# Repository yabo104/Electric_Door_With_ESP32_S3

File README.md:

# Controlador de Portón — ESP32-S3

Controlador electrónico para automatizar la apertura y cierre de un portón residencial, con
firmware propio (ESP32-S3) y placa controladora diseñada a medida (KiCad).

Mueve el motor mediante dos relevos (sentido) y un TRIAC (potencia, por ángulo de fase
sincronizado al cruce por cero de la red), lee finales de carrera y un sensor de efecto Hall para
detectar movimiento/atasco, y decodifica un control remoto RF 433MHz.

## Estado actual

**Funcional en hardware real** — validado de punta a punta en un portón físico:

- Apertura y cierre con un solo botón del control remoto, con inversión de sentido y detención
  parcial (doble pulsación) para dejar pasar personas o vehículos sin abrir del todo.
- Interlock de seguridad: nunca ambos relevos activos a la vez, el motor siempre se detiene antes
  de invertir sentido.
- Detección de atasco por ausencia de pulsos del sensor de movimiento, con estado de falla y
  reset manual por un botón dedicado.
- Disparo del TRIAC por ángulo de fase, sincronizado al cruce por cero de la red — hoy en un
  **nivel de potencia fijo**, calibrado empíricamente en el portón real (ver *Limitaciones*).
- Indicador LED (encendido en movimiento, parpadeo al confirmar cada final de carrera) y un
  contador de pulsos por trayecto, pensado como base para una futura calibración de recorrido.
- Sin Wi-Fi ni Bluetooth: los dos radios se apagan explícitamente al arrancar.

### Limitaciones conocidas

- **Sin arranque/parada suaves todavía.** El disparo por ángulo de fase está implementado y
  funcionando, pero corre a potencia constante — la rampa gradual (arranque suave) quedó
  pospuesta: en las pruebas, disparar muy cerca del cruce por cero no enganchaba el TRIAC de
  forma confiable con este motor (carga inductiva), y la rampa pasaba por esa zona. La parada
  sigue siendo instantánea.
- El `timeout` de detección de atasco sigue en un valor ajustado empíricamente, no derivado
  analíticamente.
- El diseño de la placa (carpeta de KiCad) está en proceso de renombrado; los archivos de
  fabricación (gerbers/BOM) pueden no reflejar la última revisión del esquemático.

## Estructura del repositorio

- **`Firmware_Porton/`** — firmware, proyecto [PlatformIO](https://platformio.org/) (entorno
  `esp32-s3-devkitc-1`, framework Arduino).
- **`PCB_Door_Controller/`** — diseño de la placa controladora en KiCad.
- **`Docs/`** — datasheets y referencias de los componentes usados (driver TRIAC, convertidor
  DC-DC, módulo de alimentación).
- **`bitacora/`** — documentación de continuidad del proyecto (decisiones, arquitectura,
  histórico de sesiones de desarrollo) bajo el marco [stele](https://github.com/emezav/stele).

## Hardware

| Componente | Detalle |
| --- | --- |
| Módulo | ESP32-S3-WROOM-1U-N8R8 |
| Motor | AC 110V, fase partida (con capacitor de arranque) |
| Potencia | TRIAC BT138-800, disparo por ángulo de fase sincronizado a cruce por cero |
| Sentido | 2 relevos (interlock por software: nunca ambos activos) |
| Posición | 2 finales de carrera (reed switch) + sensor de efecto Hall |
| Control remoto | Receptor RF 433MHz (decodificado externamente, el ESP32-S3 lee canales digitales) |

## Arranque de desarrollo

```bash
cd Firmware_Porton
pio run                              # compilar
pio run -t upload --upload-port COMx # cargar a la placa
pio device monitor -p COMx -b 115200 # monitor serie (o el USB CDC nativo del ESP32-S3)
```

## Licencia

Sin definir todavía.

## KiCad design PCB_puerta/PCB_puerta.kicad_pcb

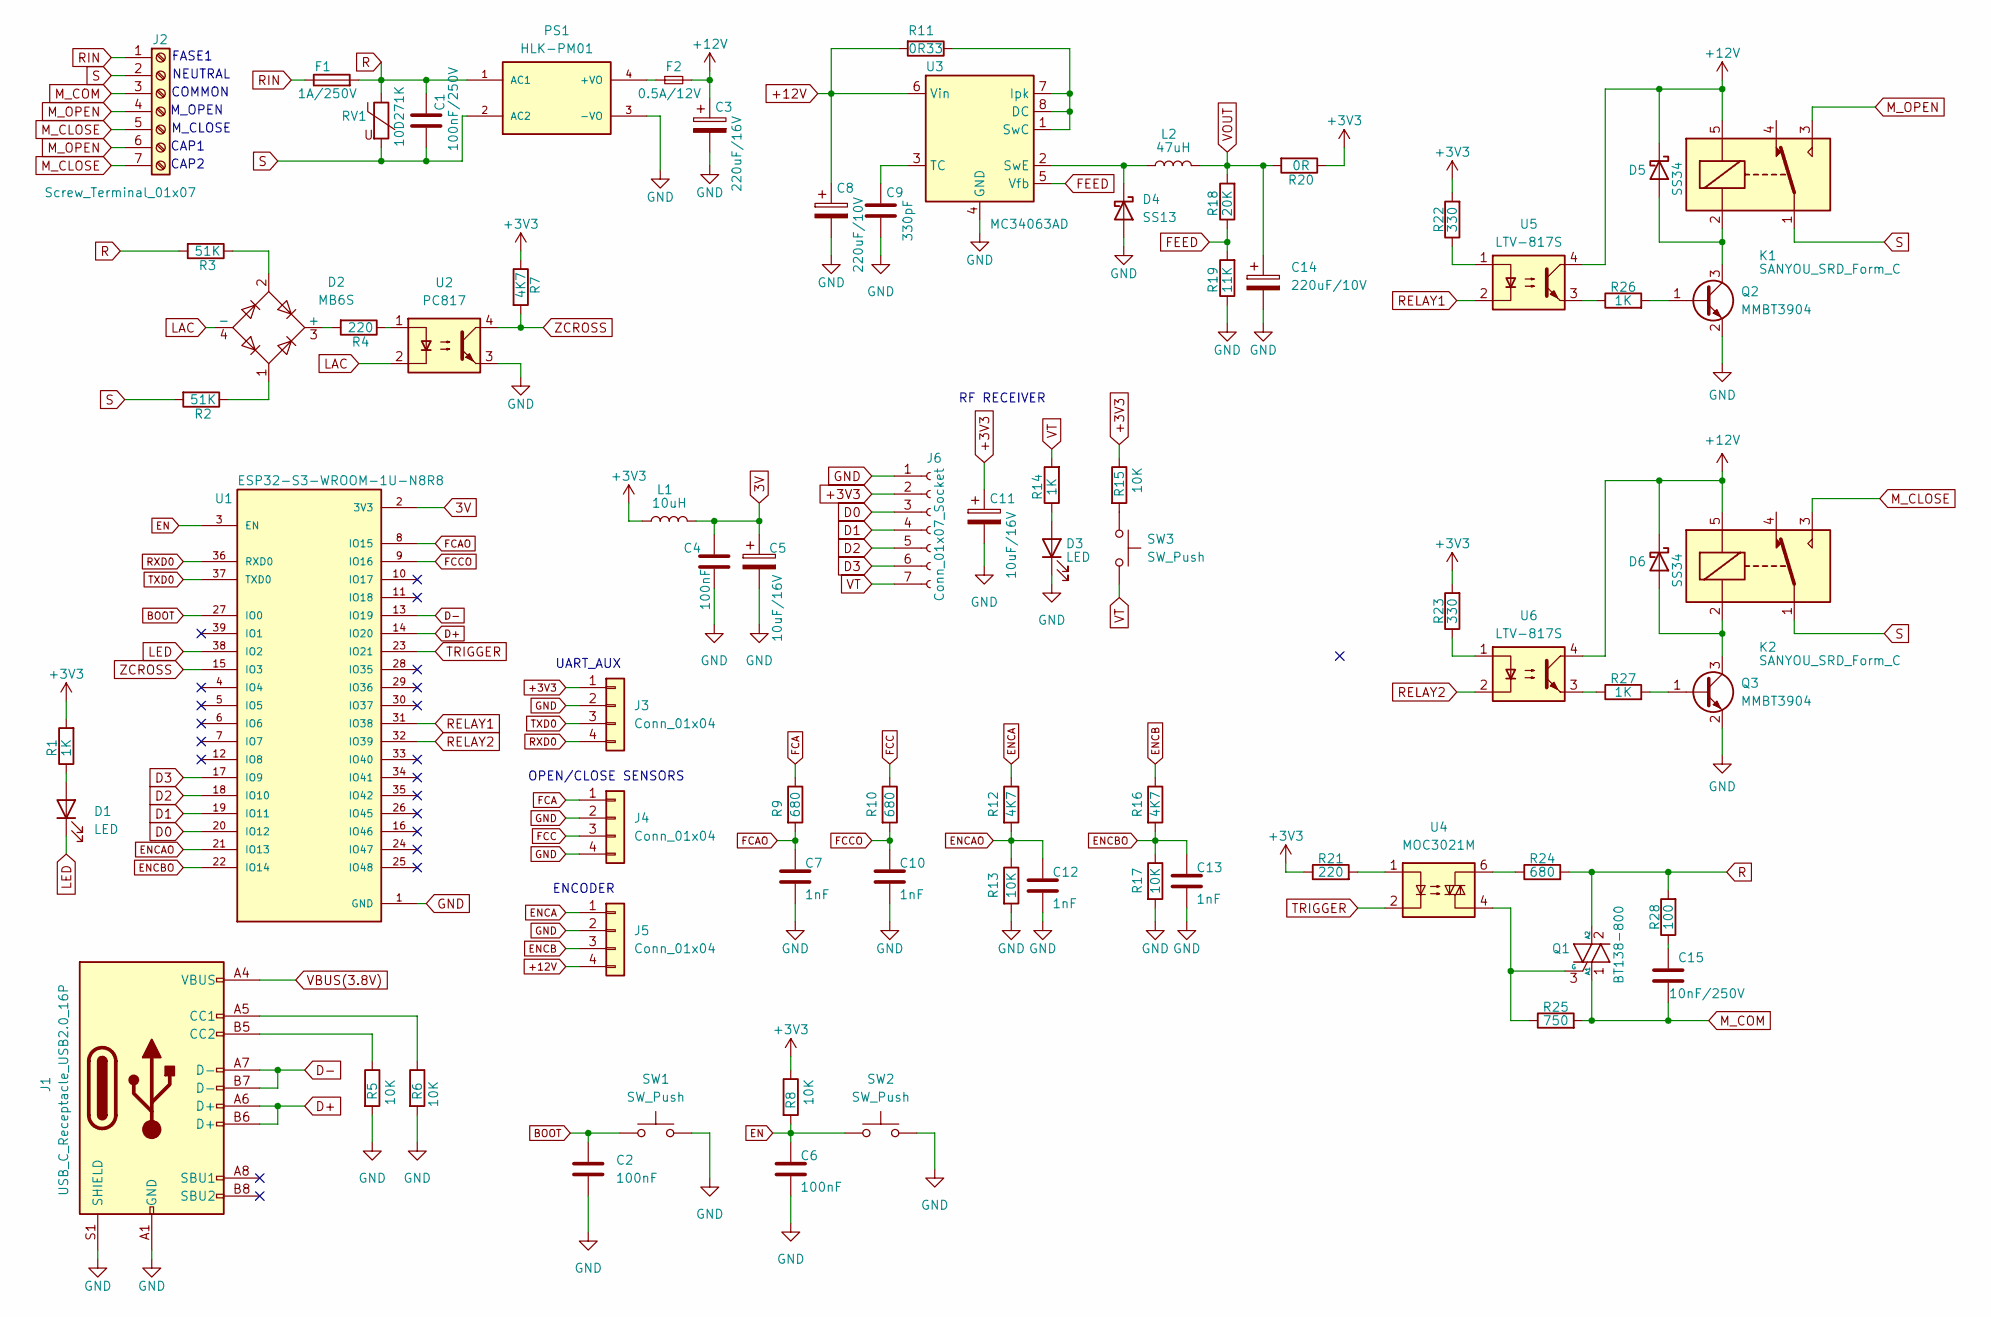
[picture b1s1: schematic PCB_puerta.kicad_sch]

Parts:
C1: 100nF/250V; C_Disc_D10.5mm_W5.0mm_P7.50mm
C2, C4, C6: 100nF; C_0603_1608Metric
C3: 220uF/16V; CP_Elec_6.3x7.7
C5, C11: 10uF/16V; CP_EIA-3216-10_Kemet-I
C7, C10, C12, C13: 1nF; C_0603_1608Metric
C8, C14: 220uF/10V; CP_Elec_6.3x7.7
C9: 330pF; C_0603_1608Metric
C15: 10nF/250V; C_Disc_D7.5mm_W5.0mm_P7.50mm
D1, D3: LED; LED_0805_2012Metric
D2: MB6S; TO-269AA
D4: SS13; D_SMA
D5, D6: SS34; D_SMA
F1: 1A/250V; Fuseholder_Clip-5x20mm_Littelfuse_445-030_Inline_P20.50x5.2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
F2: 0.5A/12V; Fuse_0805_2012Metric
J1: USB_C_Receptacle_USB2.0_16P; USB_C_Receptacle_GCT_USB4105-xx-A_16P_TopMnt_Horizontal
J2: Screw_Terminal_01x07; TerminalBlock_MaiXu_MX126-5.0-07P_1x07_P5.00mm
J3, J4: Conn_01x04; JST_PH_B4B-PH-K_1x04_P2.00mm_Vertical
J5: Conn_01x04; Molex_KK-254_AE-6410-04A_1x04_P2.54mm_Vertical
J6: Conn_01x07_Socket; PinHeader_1x07_P2.54mm_Vertical
K1, K2: SANYOU_SRD_Form_C; Relay_SPDT_SANYOU_SRD_Series_Form_C
L1: 10uH; L_0603_1608Metric
L2: 47uH; L_Changjiang_FXL0624
PS1: HLK-PM01; CONV_HLK-PM01
Q1: BT138-800; TO-220-3_Vertical
Q2, Q3: MMBT3904; SOT-23
R1, R14: 1K; R_0603_1608Metric
R2, R3: 51K; R_0603_1608Metric
R4: 220; R_0603_1608Metric
R5, R6, R8, R13, R15, R17: 10K; R_0603_1608Metric
R7, R12, R16: 4K7; R_0603_1608Metric
R9, R10: 680; R_0603_1608Metric
R11: 0R33; R_0603_1608Metric
R18: 20K; R_0603_1608Metric
R19: 11K; R_0603_1608Metric
R20: 0R; R_0603_1608Metric
R21: 220; R_0603_1608Metric_Pad0.98x0.95mm_HandSolder
R22, R23: 330; R_0603_1608Metric_Pad0.98x0.95mm_HandSolder
R24: 680; R_0603_1608Metric_Pad0.98x0.95mm_HandSolder
R25: 750; R_0603_1608Metric_Pad0.98x0.95mm_HandSolder
R26, R27: 1K; R_0603_1608Metric_Pad0.98x0.95mm_HandSolder
R28: 100; R_Axial_DIN0414_L11.9mm_D4.5mm_P15.24mm_Horizontal
RV1: 10D271K; RV_Disc_D12mm_W3.9mm_P7.5mm
SW1, SW2, SW3: SW_Push; SW_Tactile_SPST_NO_Straight_CK_PTS636Sx25SMTRLFS
U1: ESP32-S3-WROOM-1U-N8R8; ESP32-S3-WROOM-1; PARTREV v1.1
U2: PC817; SMDIP-4_W9.53mm
U3: MC34063AD; SOIC-8_3.9x4.9mm_P1.27mm
U4: MOC3021M; DIP-6_W7.62mm_LongPads
U5, U6: LTV-817S; SMDIP-4_W9.53mm

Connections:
3V: C4.1, C5.1, L1.2, U1.2 (3V3)
+3V3: C11.1, J3.1, J6.2, L1.1, R1.2, R7.1, R8.1, R15.1, R20.1, R21.1, R22.2, R23.2
+12V: C3.1, C8.1, D5.1 (K), D6.1 (K), F2.2, J5.4, K1.5, K2.5, R11.2, U3.6 (Vin), U5.4, U6.4
BOOT: C2.1, SW1.1, U1.27 (IO0)
D0: J6.3, U1.20 (IO12)
D1: J6.4, U1.19 (IO11)
D2: J6.5, U1.18 (IO10)
D3: J6.6, U1.17 (IO9)
D+: J1.A6 (D+), J1.B6 (D+), U1.14 (IO20)
D-: J1.A7 (D-), J1.B7 (D-), U1.13 (IO19)
EN: C6.1, R8.2, SW2.1, U1.3 (EN)
ENCA: J5.1, R12.1
ENCAO: C12.1, R12.2, R13.1, U1.21 (IO13)
ENCB: J5.3, R16.1
ENCBO: C13.1, R16.2, R17.1, U1.22 (IO14)
FCA: J4.1, R9.1
FCAO: C7.1, R9.2, U1.8 (IO15)
FCC: J4.3, R10.1
FCCO: C10.1, R10.2, U1.9 (IO16)
FEED: R18.1, R19.2, U3.5 (Vfb)
GND: C2.2, C3.2, C4.2, C5.2, C6.2, C7.2, C8.2, C9.2, C10.2, C11.2, C12.2, C13.2, C14.2, D3.1 (K), D4.2 (A), J1.A1 (GND), J1.A12 (GND), J1.B1 (GND), J1.B12 (GND), J1.S1 (SHIELD), J3.2, J4.2, J4.4, J5.2, J6.1, PS1.3 (-VO), Q2.2 (E), Q3.2 (E), R5.2, R6.2, R13.2, R17.2, R19.1, SW1.2, SW2.2, U1.1 (GND), U1.40 (GND), U1.41_1 (GND), U1.41_2 (GND), U1.41_3 (GND), U1.41_4 (GND), U1.41_5 (GND), U1.41_6 (GND), U1.41_7 (GND), U1.41_8 (GND), U1.41_9 (GND), U2.3, U3.4 (GND)
LAC: D2.4 (-), U2.2
LED: D1.1 (K), U1.38 (IO2)
M_CLOSE: J2.5, J2.7, K2.3
M_COM: C15.2, J2.3, Q1.1 (A1), R25.2
M_OPEN: J2.4, J2.6, K1.3
unnamed: C15.1, R28.1
unnamed: D1.2 (A), R1.1
unnamed: D2.3 (+), R4.2
unnamed: D2.1, R2.1
unnamed: D2.2, R3.1
unnamed: D3.2 (A), R14.1
unnamed: D4.1 (K), L2.1, U3.2 (SwE)
unnamed: D5.2 (A), K1.2, Q2.3 (C)
unnamed: D6.2 (A), K2.2, Q3.3 (C)
unnamed: J1.A5 (CC1), R6.1
unnamed: J1.B5 (CC2), R5.1
unnamed: F2.1, PS1.4 (+VO)
unnamed: Q1.3 (G), R25.1, U4.4
unnamed: Q2.1 (B), R26.2
unnamed: Q3.1 (B), R27.2
unnamed: R4.1, U2.1
unnamed: R15.2, SW3.1
unnamed: R21.2, U4.1
unnamed: R22.1, U5.1
unnamed: R23.1, U6.1
unnamed: R24.1, U4.6
unnamed: R26.1, U5.3
unnamed: R27.1, U6.3
unnamed: R11.1, U3.1 (SwC), U3.7 (Ipk), U3.8 (DC)
unnamed: C9.1, U3.3 (TC)
R: C1.1, F1.2, PS1.1 (AC1), Q1.2 (A2), R3.2, R24.2, R28.2, RV1.1
RELAY1: U1.31 (IO38), U5.2
RELAY2: U1.32 (IO39), U6.2
RIN: F1.1, J2.1
RXD0: J3.4, U1.36 (RXD0)
S: C1.2, J2.2, K1.1, K2.1, PS1.2 (AC2), R2.2, RV1.2
TRIGGER: U1.23 (IO21), U4.2
TXD0: J3.3, U1.37 (TXD0)
VBUS(3.8V): J1.A4 (VBUS), J1.A9 (VBUS), J1.B4 (VBUS), J1.B9 (VBUS)
VOUT: C14.1, L2.2, R18.2, R20.2
VT: J6.7, R14.2, SW3.2
ZCROSS: R7.2, U1.15 (IO3), U2.4

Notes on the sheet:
OPEN/CLOSE SENSORS
RF RECEIVER
CAP2
M_CLOSE
FASE1
CAP1
M_OPEN
ENCODER
UART_AUX
NEUTRAL
COMMON

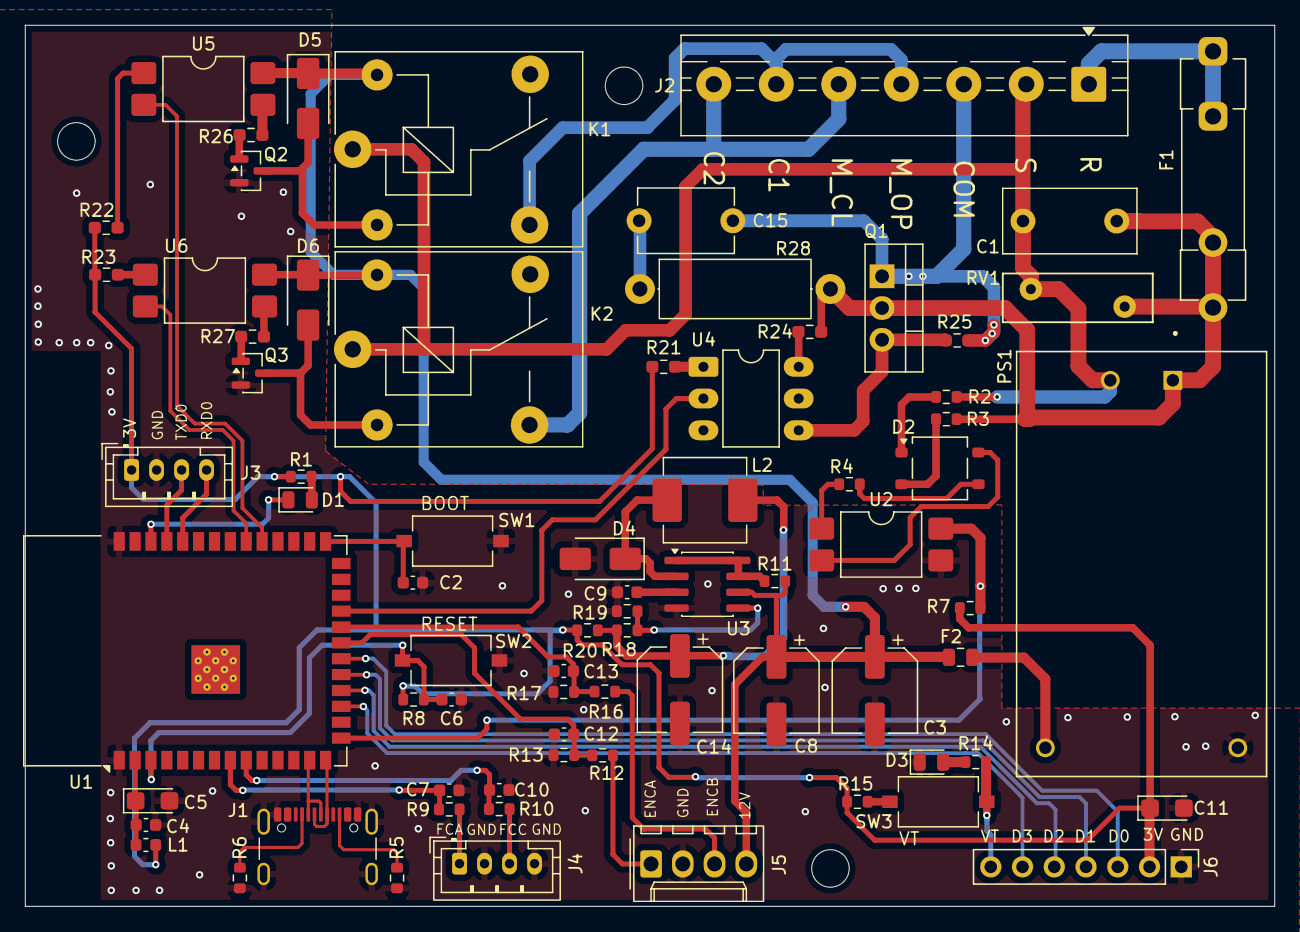
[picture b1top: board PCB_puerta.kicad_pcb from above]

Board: 2 copper layers, 99.9 x 70.5 mm, 75 parts (0 on the bottom side), 63 nets.

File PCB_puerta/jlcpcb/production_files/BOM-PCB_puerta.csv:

Comment,Designator,Footprint,LCSC,Quantity
220,R21,R_0603_1608Metric_Pad0.98x0.95mm_HandSolder,,1
220uF/16V,C3,CP_Elec_6.3x7.7,,1
10K2,R6,R_0603_1608Metric,,1
MB6S,D2,TO-269AA,,1
1nF,C7,C_0603_1608Metric,,1
51K,R3,R_0603_1608Metric,,1
4K7,R16,R_0603_1608Metric,,1
100,R28,R_Axial_DIN0414_L11.9mm_D4.5mm_P15.24mm_Horizontal,,1
10K1,R5,R_0603_1608Metric,,1
10uH,L1,L_0603_1608Metric,,1
680,R24,R_0603_1608Metric_Pad0.98x0.95mm_HandSolder,,1
0R,R20,R_0603_1608Metric,,1
51K,R2,R_0603_1608Metric,,1
BT138-800,Q1,TO-220-3_Vertical,,1
10K,R15,R_0603_1608Metric,,1
10K,R8,R_0603_1608Metric,,1
LTV-817S,U6,SMDIP-4_W9.53mm,,1
10nF/250V,C15,C_Disc_D7.5mm_W5.0mm_P7.50mm,,1
1nF,C12,C_0603_1608Metric,,1
PC817,U2,SMDIP-4_W9.53mm,,1
10D271K,RV1,RV_Disc_D12mm_W3.9mm_P7.5mm,,1
680,R10,R_0603_1608Metric,,1
LED,D1,LED_0805_2012Metric,,1
4K7,R12,R_0603_1608Metric,,1
10uF/16V,C5,CP_EIA-3216-10_Kemet-I,,1
10K,R13,R_0603_1608Metric,,1
330,R22,R_0603_1608Metric_Pad0.98x0.95mm_HandSolder,,1
MMBT3904,Q2,SOT-23,,1
SS34,D6,D_SMA,,1
750,R25,R_0603_1608Metric_Pad0.98x0.95mm_HandSolder,,1
MMBT3904,Q3,SOT-23,,1
SW_Push,SW2,SW_Tactile_SPST_NO_Straight_CK_PTS636Sx25SMTRLFS,,1
SW_Push,SW3,SW_Tactile_SPST_NO_Straight_CK_PTS636Sx25SMTRLFS,,1
0.5A/12V,F2,Fuse_0805_2012Metric,,1
1K,R1,R_0603_1608Metric,,1
4K7,R7,R_0603_1608Metric,,1
ESP32-S3-WROOM-1U-N8R8,U1,ESP32-S3-WROOM-1,,1
220,R4,R_0603_1608Metric,,1
0R33,R11,R_0603_1608Metric,,1
10K,R17,R_0603_1608Metric,,1
10uF/16V,C11,CP_EIA-3216-10_Kemet-I,,1
220uF/10V,C14,CP_Elec_6.3x7.7,,1
HLK-PM01,PS1,CONV_HLK-PM01,,1
680,R9,R_0603_1608Metric,,1
1A/250V,F1,Fuseholder_Clip-5x20mm_Littelfuse_445-030_Inline_P20.50x5.20mm_D1.30mm_Horizontal,,1
USB_C_Receptacle_USB2.0_16P,J1,USB_C_Receptacle_GCT_USB4105-xx-A_16P_TopMnt_Horizontal,,1
MC33063AD,U3,SOIC-8_3.9x4.9mm_P1.27mm,,1
100nF/250V,C1,C_Disc_D10.5mm_W5.0mm_P7.50mm,,1
100nF,C2,C_0603_1608Metric,,1
330pF,C9,C_0603_1608Metric,,1
330,R23,R_0603_1608Metric_Pad0.98x0.95mm_HandSolder,,1
Conn_01x04,J4,JST_PH_B4B-PH-K_1x04_P2.00mm_Vertical,,1
Conn_01x07_Socket,J6,PinHeader_1x07_P2.54mm_Vertical,,1
SANYOU_SRD_Form_C,K1,Relay_SPDT_SANYOU_SRD_Series_Form_C,,1
1nF,C10,C_0603_1608Metric,,1
20K,R18,R_0603_1608Metric,,1
100nF,C4,C_0603_1608Metric,,1
LED,D3,LED_0805_2012Metric,,1
SANYOU_SRD_Form_C,K2,Relay_SPDT_SANYOU_SRD_Series_Form_C,,1
SS34,D5,D_SMA,,1
1nF,C13,C_0603_1608Metric,,1
LTV-817S,U5,SMDIP-4_W9.53mm,,1
SW_Push,SW1,SW_Tactile_SPST_NO_Straight_CK_PTS636Sx25SMTRLFS,,1
1K,R26,R_0603_1608Metric_Pad0.98x0.95mm_HandSolder,,1
MOC3021M,U4,DIP-6_W7.62mm_LongPads,,1
220uF/10V,C8,CP_Elec_6.3x7.7,,1
10K,R19,R_0603_1608Metric,,1
47uH,L2,L_Changjiang_FXL0624,,1
100nF,C6,C_0603_1608Metric,,1
SS13,D4,D_SMA,,1
1K,R27,R_0603_1608Metric_Pad0.98x0.95mm_HandSolder,,1
Screw_Terminal_01x07,J2,TerminalBlock_MaiXu_MX126-5.0-07P_1x07_P5.00mm,,1
Conn_01x04,J3,JST_PH_B4B-PH-K_1x04_P2.00mm_Vertical,,1
Conn_01x04,J5,Molex_KK-254_AE-6410-04A_1x04_P2.54mm_Vertical,,1
1K,R14,R_0603_1608Metric,,1

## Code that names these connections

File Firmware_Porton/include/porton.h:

#ifndef PORTON_H
#define PORTON_H

#include <Arduino.h>

/* Salida LED / BUZZER. Activo en LOW. */
#define LED         2
/* Cruce por cero de la AC. Sincroniza el disparo del TRIAC por angulo de fase (ver
   RAMPA_ARRANQUE_MS mas abajo). */
#define ZCROSS      3

/* Entradas del receptor RF 433MHz.
   D0 = abrir/cerrar/invertir/detener (control normal). D2 = salir de ERROR unicamente.
   D1/D3 sin uso por ahora. */
#define D3          9
#define D2          10
#define D1          11
#define D0          12

/* Encoder del motor. Por ahora solo se usa ENCA, como pulso de "el motor se esta moviendo". */
#define ENCA        13
#define ENCB        14

/* Finales de carrera (reed switch). Normalmente en alto; activos en LOW. */
#define FC_OPEN     15
#define FC_CLOSE    16

/* Disparo del TRIAC (BT138-800). Activo en LOW. Pulso de gate corto (PULSO_TRIAC_US), disparado
   por angulo de fase desde ZCROSS -- no se mantiene fijo en LOW como antes. */
#define TRIGGER     21

/* Relevos de sentido. Activos en LOW. NUNCA ambos activos a la vez (ver seleccionarSentido()
   en porton.cpp: siempre escribe los dos pines juntos, nunca uno solo). */
#define RELAY_OP    38
#define RELAY_CL    39

/* Tiempos de la maquina de estados, en milisegundos. */
#define RELAY_SETTLE_MS     500   // entre elegir sentido (relevo) y habilitar potencia (TRIAC)
#define REVERSE_STOP_MS     500   // detenido obligatorio antes de invertir sentido
#define ENCODER_TIMEOUT_MS  2000  // TEMPORAL (subido para diagnosticar el encoder con
                                    // osciloscopio) -- volver a un valor real (unos segundos)
                                    // antes de dar por buena la deteccion de atasco.
#define BOTON_DEBOUNCE_MS   80    // antirrebote de D0/D2
#define DOBLE_PULSACION_MS  2000  // ventana para detectar doble pulsacion de D0 en movimiento
                                   // (detiene y deja el porton a medio camino, sin invertir)
#define LED_PAUSA_PARPADEO_MS 100 // apagado visible antes del parpadeo (para que se note el
                                   // flanco: el LED ya viene encendido fijo por el movimiento)
#define LED_PARPADEO_MS     150   // duracion del parpadeo del LED al detectar un fin de carrera

/* Antirrebote del pulso de ZCROSS, en microsegundos. El comparador analogico puede generar mas
   de un flanco de subida muy cercano en el mismo cruce (confirmado con osciloscopio: la senal
   real es limpia, ~120,8Hz, pero el firmware seguia contando ~2x con 1000us de antirrebote). Se
   ignoran flancos que lleguen antes de este tiempo desde el ultimo aceptado. 3000us sigue con
   margen de sobra frente a los ~8333us entre cruces reales a 60Hz, y evita que un flanco espurio
   arme el disparo del TRIAC dos veces para el mismo cruce real. */
#define ZCROSS_DEBOUNCE_US  3000

/* --- Disparo del TRIAC por angulo de fase ---
   SEMICICLO_US: duracion aproximada de un semiciclo de red a 60Hz (confirmado: ZCROSS mide
   ~120,8Hz = 2x60Hz). Referencia para los otros valores, no es un limite duro en el codigo.
   PULSO_TRIAC_US: ancho del pulso de gate del BT138-800. 500us (subido desde 200us en la sesion
   008: un pulso mas largo ayuda a enganchar con esta carga inductiva, sobre todo cerca del cruce
   por cero). El retardo (DISPARO_US_MAX/MIN) y el ancho del pulso son independientes: el pulso
   puede durar mas que el retardo sin problema, el TRIAC solo necesita el gate en LOW el tiempo
   suficiente para enganchar.
   DISPARO_US_MAX: retardo de disparo en la potencia mas alta que se usa (chico = cerca del cruce
   por cero = mas conduccion).

   ESTADO ACTUAL (sesion 008): **release en potencia fija, sin rampa de arranque suave.** La
   version original de esta seccion armaba una rampa (DISPARO_US_MIN bajo -> DISPARO_US_MAX)
   durante RAMPA_ARRANQUE_MS. En las pruebas de banco con el porton real, disparar demasiado cerca
   del cruce por cero (potencias ~100%) no siempre enganchaba el TRIAC con esta carga inductiva, y
   la rampa pasaba por esa zona marginal -- eso generaba paradas falsas por "atasco" durante el
   arranque. Se decidio, con el usuario, dejar el release con **potencia fija** en el nivel que sí
   demostro enganchar de forma confiable (ver POTENCIA_MOTOR_PCT abajo) y posponer la rampa de
   arranque suave a una sesion futura, ya con este piso de potencia fiable como punto de partida.
   RAMPA_ARRANQUE_MS y la logica de actualizarRampa() en porton.cpp se dejan en el codigo (no se
   usan mientras DISPARO_US_MIN == DISPARO_US_MAX) para no tener que rehacerlas desde cero. */
#define SEMICICLO_US        8333
#define PULSO_TRIAC_US      500
#define DISPARO_US_MAX      300
#define RAMPA_ARRANQUE_MS   1200

/* --- Nivel de potencia del release (fijo, sin rampa) ---
   POTENCIA_MOTOR_PCT: 0-100. Cambiar este numero y volver a compilar/cargar para ajustar la
   potencia fija que usa el porton (por ejemplo, si cambian las condiciones mecanicas del
   recorrido). Se traduce a un retardo de disparo por interpolacion LINEAL en tiempo entre
   DISPARO_US_MAX (100%) y SEMICICLO_US (0%, disparo tan tarde que casi no hay conduccion) -- OJO:
   no es un porcentaje exacto de potencia RMS (esa relacion es no lineal: el disparo cerca del
   pico de la onda aporta bastante mas energia que cerca del cruce por cero), pero es una perilla
   monotona: mas alto = mas potencia real.
   Historial de pruebas en banco que llevaron al valor actual (motor real, sin rampa):
     100% (300us,  ~6,5 grados desde el cruce) -> el motor NO se movio (el TRIAC no llegaba a
       enganchar tan cerca del cruce, con esta carga inductiva).
     90%  (2150us, ~46 grados) -> el motor SI se movio.
     95%  (1670us, ~36 grados) -> punto intermedio, tambien probado.
     85%  (con PULSO_TRIAC_US ya en 500us) -> nivel elegido para el release: mueve el porton de
       forma confiable en todo el recorrido, sin las paradas falsas por atasco que daban los
       niveles mas cercanos al 100%. */
#define POTENCIA_MOTOR_PCT  85
#define DISPARO_US_FIJO \
  (DISPARO_US_MAX + ((uint32_t)(SEMICICLO_US - DISPARO_US_MAX) * (100 - POTENCIA_MOTOR_PCT)) / 100)
#define DISPARO_US_MIN      DISPARO_US_FIJO

/* --- Diagnostico temporal de pulsos (ENCA/ENCB/ZCROSS/ENCA2) ---
   Para quitarlo: poner DEBUG_PULSOS en 0 (no hace falta borrar codigo). */
#define DEBUG_PULSOS        1
#define DEBUG_PULSOS_MS     1000  // cada cuanto se imprime el conteo, en ms

/* ENCA2: sensor de efecto Hall, alternativa a ENCA/ENCB (esas tienen un problema de pull-up en
   el circuito de entrada). Usa el conector auxiliar de UART0 -- GPIO44 (U0RXD) en vez de GPIO43
   (U0TXD): el ESP32-S3 solo transmite boot log / paniques por GPIO43, nunca por GPIO44, asi que
   GPIO44 queda "limpio" como entrada desde el arranque. Ninguno de los dos se usa como UART real
   (Serial usa el USB CDC nativo). Confirmado en banco (sesion 006): 0 pulsos con el motor
   quieto, pulsos reales con el motor girando -- alimenta la deteccion de atasco en paralelo con
   ENCA (ver isrEncA2 en porton.cpp), no es solo diagnostico. */
#define ENCA2       44

#if DEBUG_PULSOS
void mostrarPulsos();
#endif

enum EstadoPuerta {
  DETENIDA = 1,  // motor detenido, a la espera de un comando
  ABRIENDO = 2,
  CERRANDO = 3,
  ERROR    = 4,  // motor detenido por falla (hoy: atasco). Se sale solo con D2 (ver porton.cpp).
};

extern char comando;
extern char doorStd;
extern char doorLastStd;

void inicializarPines();
void procesarComandoSerial();
void actualizarEstadoPuerta();

#endif
